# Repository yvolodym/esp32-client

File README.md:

```bash
idf.py set-target esp32-c3
idf.py build
idf.py -p /dev/ttyUSB0 flash monitor
```

ESP-NOW spezifisch:

CONFIG_ESPNOW_ENABLE=y - ESP-NOW aktiviert
CONFIG_ESPNOW_MAX_ENCRYPT_PEER_NUM=6 - Max. verschlüsselte Peers

Wichtige ESP32-C3 spezifische Einstellungen:

Ändere die server_mac Variable mit der MAC-Adresse deines Servers
Beide Geräte müssen auf Kanal 1 sein (oder ändere ESPNOW_WIFI_CHANNEL)

Single-Core (UNICORE) - C3 hat nur einen Core
RISC-V Architektur
Optimierte IRAM-Nutzung für WiFi
WPA3 Support aktiviert

Die Konfiguration ist optimiert für:

Niedrigen Stromverbrauch
Gute WiFi-Performance
ESP-NOW Kommunikation

### PINs
```
Motor Output 1: GPIO2
Motor Output 2: GPIO3
Input 1:        GPIO4
Input 2:        GPIO5
Sleep/Enable:   GPIO6
```

### URL
* https://github.com/EzerLonginus/CH340E_USB_UART
* https://community.element14.com/technologies/open-source-hardware/b/blog/posts/ch340-building-yet-another-usb-c-to-uart-adapter-board
* https://github.com/SolderedElectronics/USB-UART-CH340C-converter-board-hardware-design
* https://hci.rwth-aachen.de/lipo

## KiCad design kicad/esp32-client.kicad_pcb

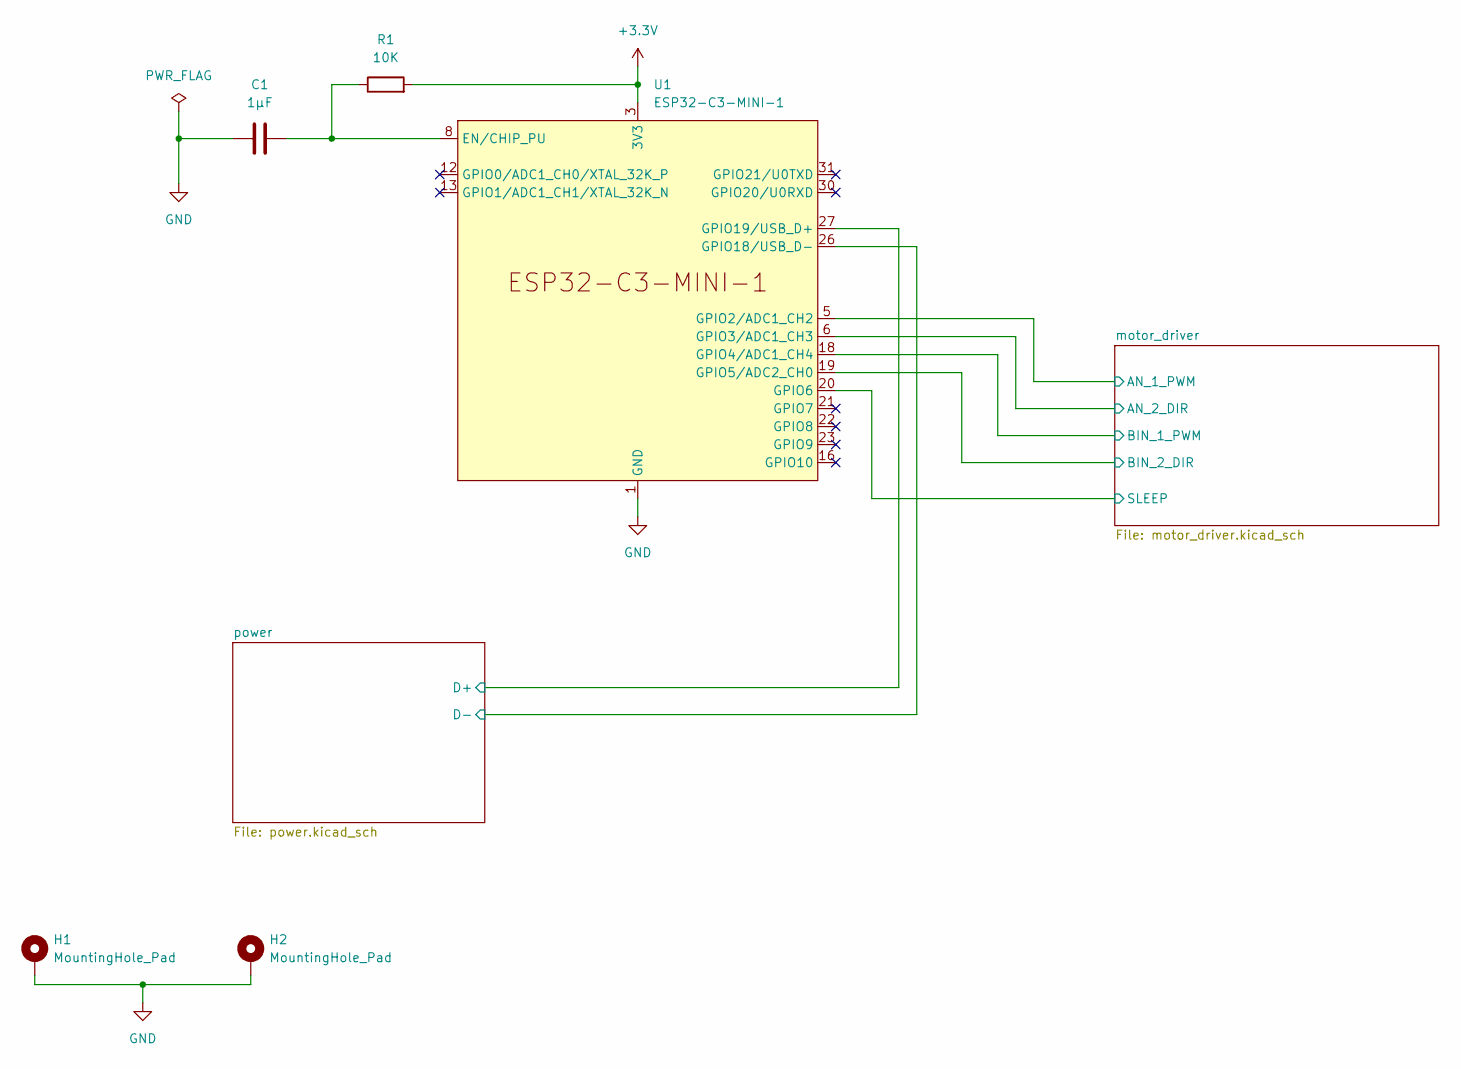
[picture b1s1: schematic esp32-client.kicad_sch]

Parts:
C1: 1µF; C_1206_3216Metric
H1, H2: MountingHole_Pad; MountingHole_2.5mm
R1: 10K; R_1206_3216Metric
U1: ESP32-C3-MINI-1

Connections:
+3.3V: R1.2, U1.3 (3V3); also elsewhere on the board
/motor_driver/AN_1_PWM: U1.5 (GPIO2/ADC1_CH2); also elsewhere on the board
/motor_driver/AN_2_DIR: U1.6 (GPIO3/ADC1_CH3); also elsewhere on the board
/motor_driver/BIN_1_PWM: U1.18 (GPIO4/ADC1_CH4); also elsewhere on the board
/motor_driver/BIN_2_DIR: U1.19 (GPIO5/ADC2_CH0); also elsewhere on the board
/motor_driver/SLEEP: U1.20 (GPIO6); also elsewhere on the board
/power/D+: U1.27 (GPIO19/USB_D+); also elsewhere on the board
/power/D-: U1.26 (GPIO18/USB_D-); also elsewhere on the board
GND: C1.2, H1.1, H2.1, U1.1 (GND), U1.2 (GND), U1.11 (GND), U1.14 (GND), U1.36 (GND), U1.37 (GND), U1.38 (GND), U1.39 (GND), U1.40 (GND), U1.41 (GND), U1.42 (GND), U1.43 (GND), U1.44 (GND), U1.45 (GND), U1.46 (GND), U1.47 (GND), U1.48 (GND), U1.49 (GND), U1.50 (GND), U1.51 (GND), U1.52 (GND), U1.53 (GND); also elsewhere on the board
unnamed: C1.1, R1.1, U1.8 (EN/CHIP_PU)

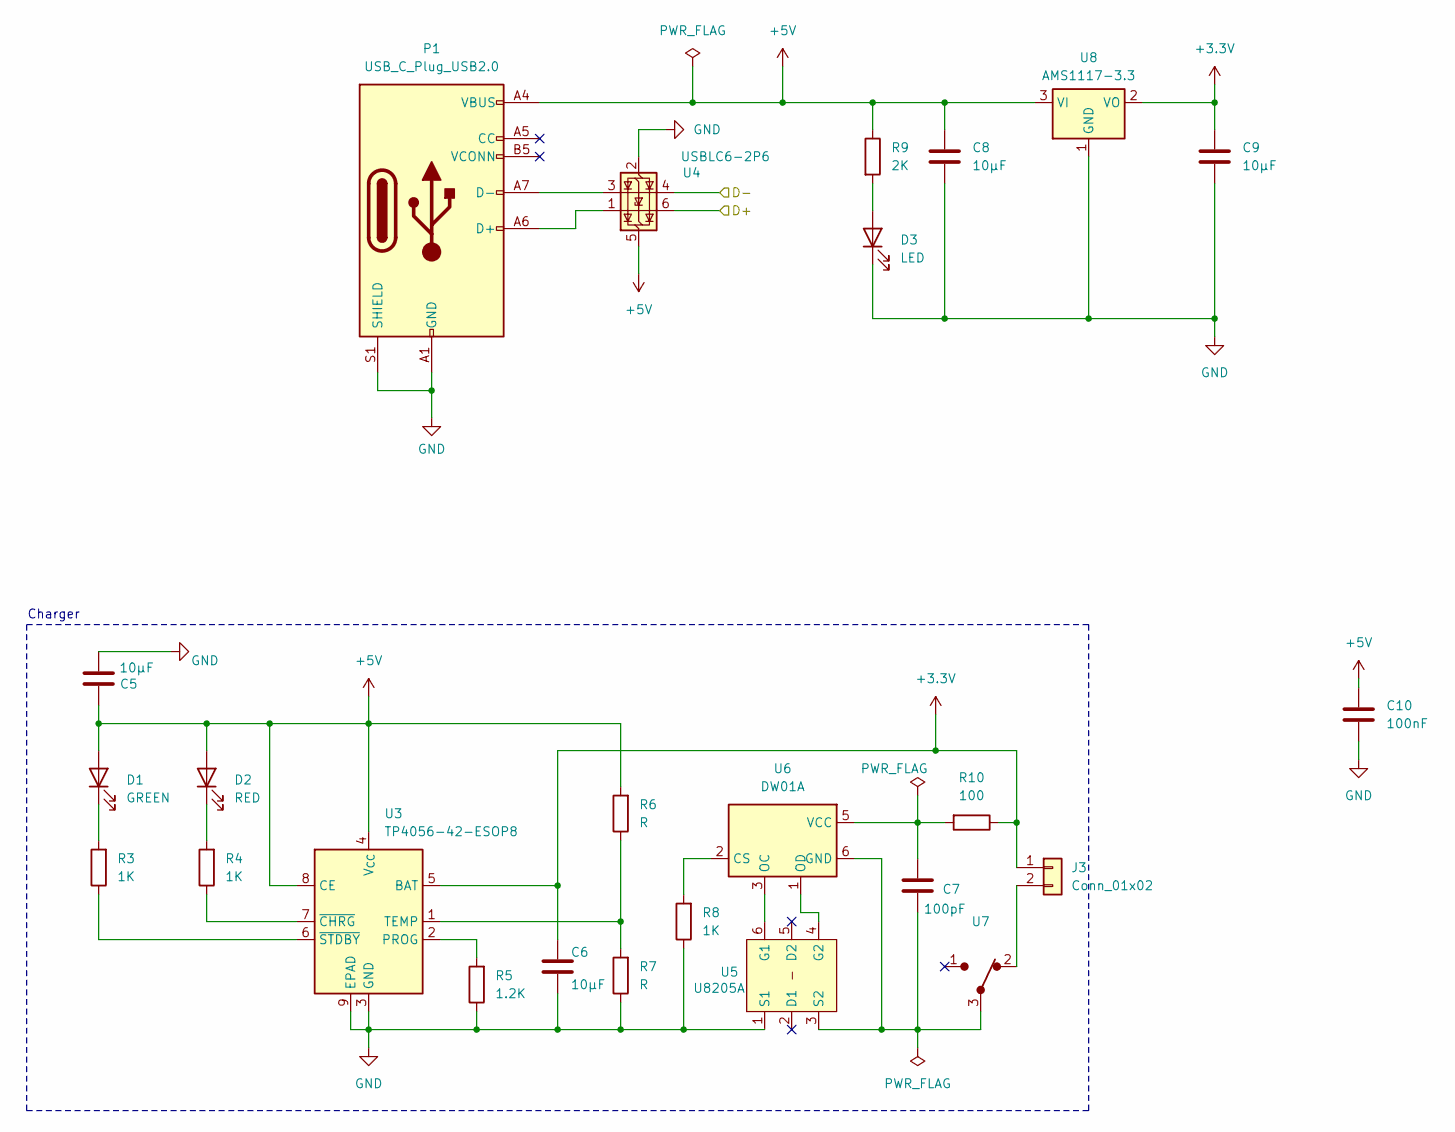
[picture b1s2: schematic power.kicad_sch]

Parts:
C5, C6, C8, C9: 10µF; C_1206_3216Metric
C7: 100pF; C_1206_3216Metric
C10: 100nF; C_1206_3216Metric
D1: GREEN; D_0603_1608Metric
D2: RED; D_0603_1608Metric
D3: LED; D_0603_1608Metric
J3: Conn_01x02; JST_PH_B2B-PH-K_1x02_P2.00mm_Vertical
P1: USB_C_Plug_USB2.0; USB_C_Receptacle_GCT_USB4105-xx-A_16P_TopMnt_Horizontal; LCSC C456012
R3, R4, R8: 1K; R_1206_3216Metric
R5: 1.2K; R_1206_3216Metric
R6, R7: R; R_1206_3216Metric
R9: 2K; R_1206_3216Metric
R10: 100; R_1206_3216Metric
U3: TP4056-42-ESOP8; SOIC-8-1EP_3.9x4.9mm_P1.27mm_EP2.41x3.3mm_ThermalVias
U4: USBLC6-2P6; SOT-23-6
U5: U8205A; SOT-23-6
U6: DW01A; SOT-23-6
U7: Switch
U8: AMS1117-3.3; SOT-223-3_TabPin2

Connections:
+3.3V: C6.1, C9.1, J3.1, R10.1, U3.5 (BAT), U8.2 (VO); also elsewhere on the board
+5V: C5.1, C8.1, C10.2, D1.2 (A), D2.2 (A), P1.A4 (VBUS), P1.A9 (VBUS), P1.B4 (VBUS), P1.B9 (VBUS), R6.2, R9.1, U3.4 (V_{CC}), U3.8 (CE), U4.5 (VBUS), U8.3 (VI)
/power/D+: U4.6 (I/O1); also elsewhere on the board
/power/D-: U4.4 (I/O2); also elsewhere on the board
GND: C5.2, C6.2, C8.2, C9.2, C10.1, D3.1 (K), P1.A1 (GND), P1.A12 (GND), P1.B1 (GND), P1.B12 (GND), P1.S1 (SHIELD), R5.1, R7.1, R8.1, U3.3 (GND), U3.9 (EPAD), U4.2 (GND), U5.1 (S1), U8.1 (GND); also elsewhere on the board
unnamed: D1.1 (K), R3.2
unnamed: D2.1 (K), R4.2
unnamed: D3.2 (A), R9.2
unnamed: J3.2, U7.2
unnamed: P1.A6 (D+), U4.1 (I/O1)
unnamed: P1.A7 (D-), U4.3 (I/O2)
unnamed: R5.2, U3.2 (PROG)
unnamed: R6.1, R7.2, U3.1 (TEMP)
unnamed: R4.1, U3.7 (~CHRG)
unnamed: R3.1, U3.6 (~STDBY)
unnamed: U5.6 (G1), U6.3 (OC)
unnamed: U5.4 (G2), U6.1 (OD)
unnamed: C7.1, U5.3 (S2), U6.6 (GND), U7.3
unnamed: R8.2, U6.2 (CS)
unnamed: C7.2, R10.2, U6.5 (VCC)

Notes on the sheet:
Charger

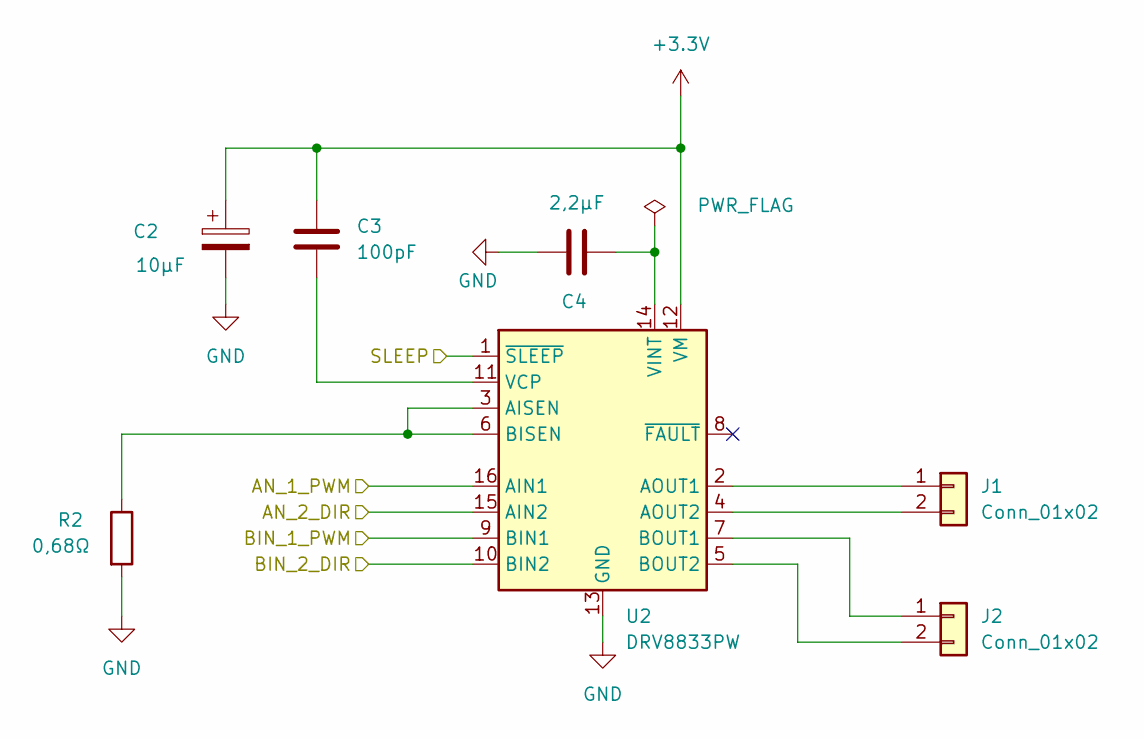
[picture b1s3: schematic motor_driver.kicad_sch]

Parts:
C2: 10µF; CP_Elec_4x3.9
C3: 100pF; C_1206_3216Metric
C4: 2,2µF; C_1206_3216Metric
J1, J2: Conn_01x02; JST_EH_B2B-EH-A_1x02_P2.50mm_Vertical
R2: 0,68Ω; R_1206_3216Metric
U2: DRV8833PW; TSSOP-16_4.4x5mm_P0.65mm

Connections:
+3.3V: C2.1, C3.1, U2.12 (VM); also elsewhere on the board
/motor_driver/AN_1_PWM: U2.16 (AIN1); also elsewhere on the board
/motor_driver/AN_2_DIR: U2.15 (AIN2); also elsewhere on the board
/motor_driver/BIN_1_PWM: U2.9 (BIN1); also elsewhere on the board
/motor_driver/BIN_2_DIR: U2.10 (BIN2); also elsewhere on the board
/motor_driver/SLEEP: U2.1 (~SLEEP); also elsewhere on the board
GND: C2.2, C4.1, R2.2, U2.13 (GND); also elsewhere on the board
unnamed: J1.1, U2.2 (AOUT1)
unnamed: J1.2, U2.4 (AOUT2)
unnamed: J2.1, U2.7 (BOUT1)
unnamed: J2.2, U2.5 (BOUT2)
unnamed: R2.1, U2.3 (AISEN), U2.6 (BISEN)
unnamed: C3.2, U2.11 (VCP)
unnamed: C4.2, U2.14 (VINT)

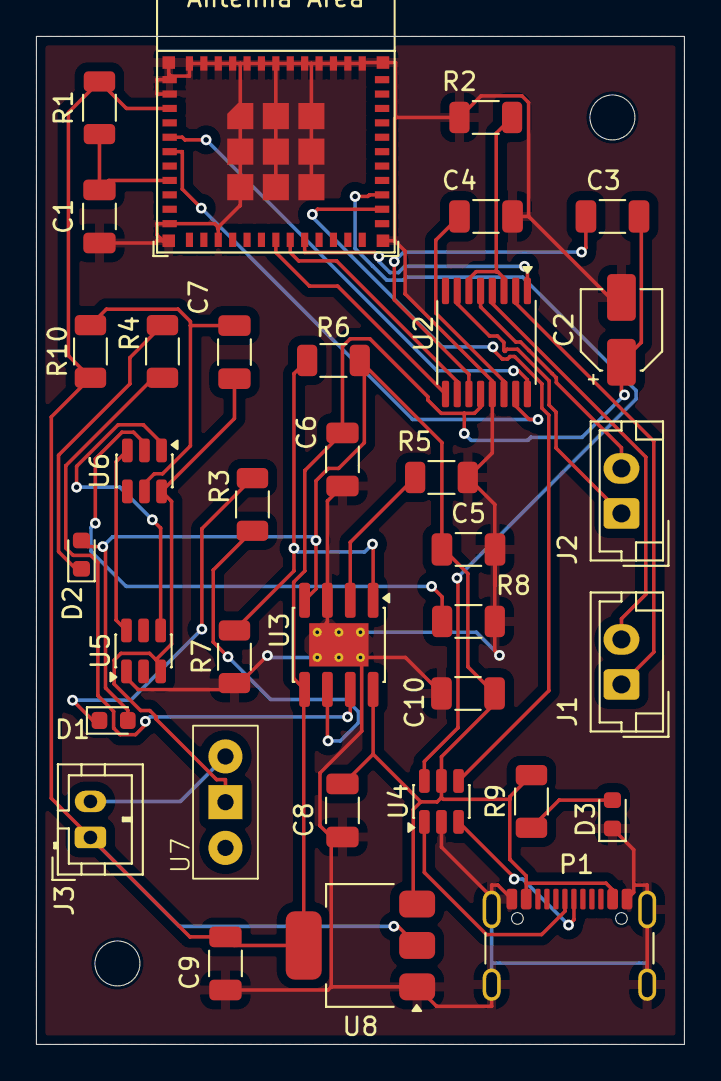
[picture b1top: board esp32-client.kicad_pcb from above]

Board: 2 copper layers, 36.0 x 56.0 mm, 37 parts (0 on the bottom side), 33 nets.

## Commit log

2025-10-18 init
